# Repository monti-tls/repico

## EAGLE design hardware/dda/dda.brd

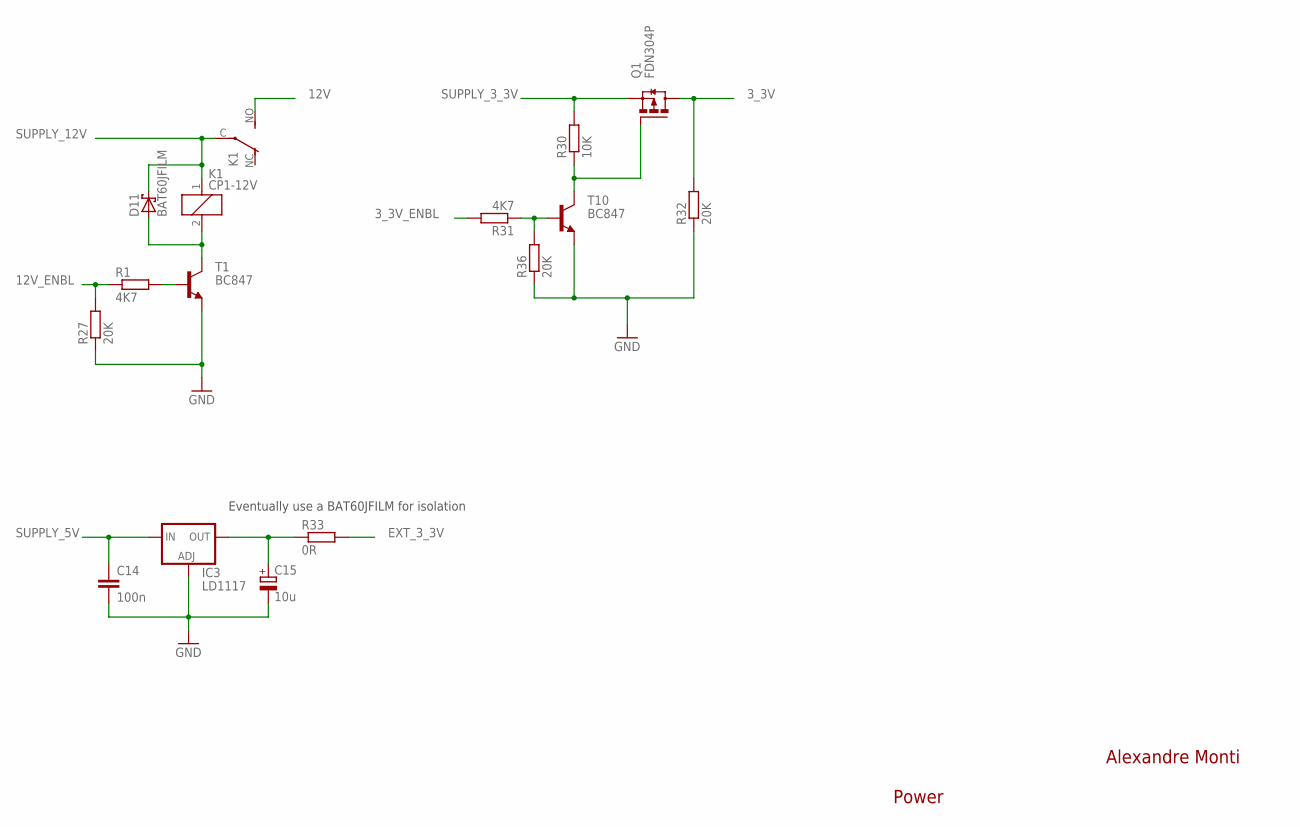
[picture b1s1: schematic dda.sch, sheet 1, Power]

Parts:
C14: 100n; C0805; PARTNO 2496944
C15: 10u; CT3216; PARTNO 1432339
D11: BAT60JFILM; SOD323_ST; PARTNO 1467544
IC3: LD1117; SOT223; PARTNO 1202826
K1: CP1-12V; CP1; PARTNO 2103582
Q1: FDN304P; SUPER-SOT3; PARTNO 9846298
R1, R31: 4K7; M0805; PARTNO 9333266
R27, R32, R36: 20K; M0805; PARTNO 9332774
R30: 10K; M0805; PARTNO 9332391
R33: 0R; R0805W; PARTNO 9333681
T1, T10: BC847; SOT23; PARTNO 2432696

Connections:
3_3V: Q1.3 (D), R32.2; also elsewhere on the board
3_3V_ENBL: R31.2; also elsewhere on the board
12V: K1.NO (S); also elsewhere on the board
12V_ENBL: R1.1, R27.2; also elsewhere on the board
EXT_3_3V: R33.2; also elsewhere on the board
GND: C14.2, C15.-, IC3.1 (ADJ), R27.1, R32.1, R36.1, T1.2 (E), T10.2 (E); also elsewhere on the board
unnamed: Q1.1 (G), R30.1, T10.3 (C)
unnamed: R31.1, R36.2, T10.1 (B)
unnamed: C15.+, IC3.4 (OUT), R33.1
unnamed: D11.A, K1.2, T1.3 (C)
unnamed: R1.2, T1.1 (B)
SUPPLY_3_3V: Q1.2 (S), R30.2; also elsewhere on the board
SUPPLY_5V: C14.1, IC3.3 (IN); also elsewhere on the board
SUPPLY_12V: D11.C, K1.1, K1.C; also elsewhere on the board

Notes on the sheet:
Alexandre Monti
Eventually use a BAT60JFILM for isolation
Power

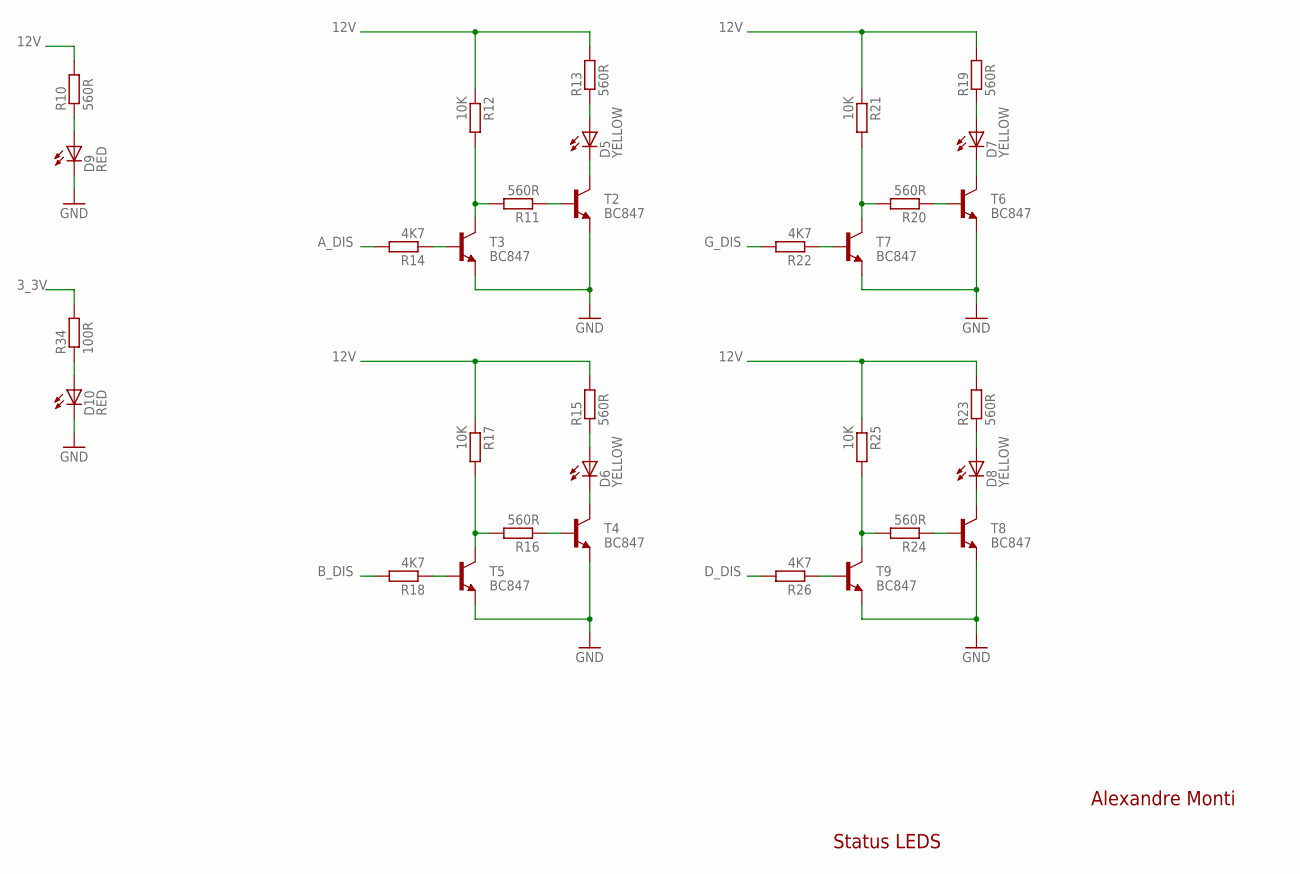
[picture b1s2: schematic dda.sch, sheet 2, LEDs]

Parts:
D5, D6, D7, D8: YELLOW; CHIP-LED0805; PARTNO 1581241
D9, D10: RED; CHIP-LED0805; PARTNO 1581239
R10, R11, R13, R15, R16, R19, R20, R23, R24: 560R; M0805; PARTNO 9334688
R12, R17, R21, R25: 10K; M0805; PARTNO 9332391
R14, R18, R22, R26: 4K7; M0805; PARTNO 9333266
R34: 100R; M0805; PARTNO 9237364
T2, T3, T4, T5, T6, T7, T8, T9: BC847; SOT23; PARTNO 2432696

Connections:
3_3V: R34.2; also elsewhere on the board
12V: R10.2, R12.1, R13.2, R15.2, R17.1, R19.2, R21.1, R23.2, R25.1; also elsewhere on the board
A_DIS: R14.2; also elsewhere on the board
B_DIS: R18.2; also elsewhere on the board
D_DIS: R26.2; also elsewhere on the board
GND: D9.C, D10.C, T2.2 (E), T3.2 (E), T4.2 (E), T5.2 (E), T6.2 (E), T7.2 (E), T8.2 (E), T9.2 (E); also elsewhere on the board
G_DIS: R22.2; also elsewhere on the board
unnamed: D10.A, R34.1
unnamed: D5.C, T2.3 (C)
unnamed: D5.A, R13.1
unnamed: R11.1, T2.1 (B)
unnamed: R11.2, R12.2, T3.3 (C)
unnamed: D6.C, T4.3 (C)
unnamed: R14.1, T3.1 (B)
unnamed: D6.A, R15.1
unnamed: R16.1, T4.1 (B)
unnamed: R16.2, R17.2, T5.3 (C)
unnamed: R18.1, T5.1 (B)
unnamed: D7.C, T6.3 (C)
unnamed: D7.A, R19.1
unnamed: R20.1, T6.1 (B)
unnamed: R20.2, R21.2, T7.3 (C)
unnamed: R22.1, T7.1 (B)
unnamed: D8.C, T8.3 (C)
unnamed: D8.A, R23.1
unnamed: R24.1, T8.1 (B)
unnamed: R24.2, R25.2, T9.3 (C)
unnamed: R26.1, T9.1 (B)
unnamed: D9.A, R10.1

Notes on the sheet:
Alexandre Monti
Status LEDS

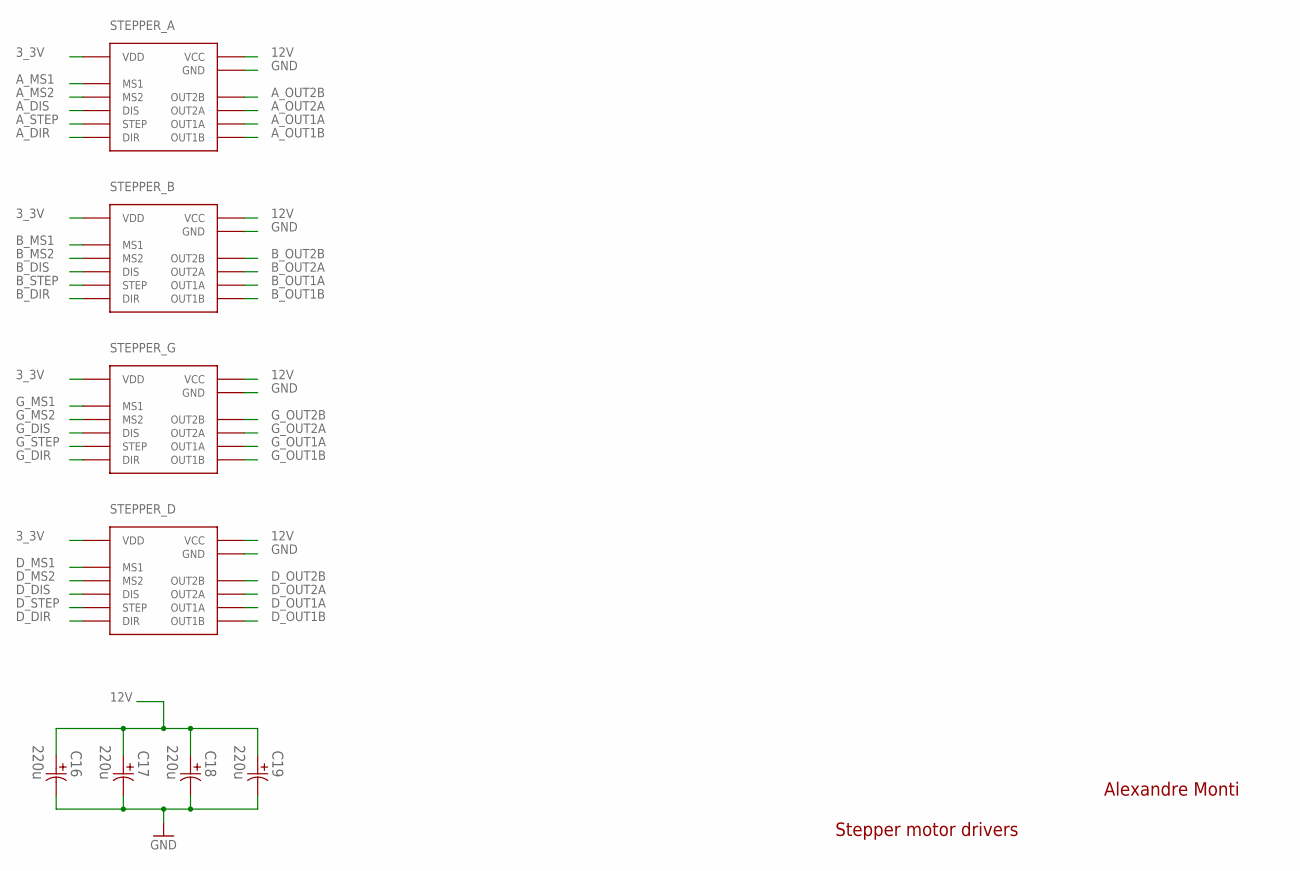
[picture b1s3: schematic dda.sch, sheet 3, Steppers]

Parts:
C16, C17, C18, C19: 220u; CAPAE660X800N; PARTNO 1868409
STEPPER_A: REPICO_STEPPER; PARTNO 1593462
STEPPER_B: REPICO_STEPPER; PARTNO 1593462
STEPPER_D: REPICO_STEPPER; PARTNO 1593462
STEPPER_G: REPICO_STEPPER; PARTNO 1593462

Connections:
3_3V: STEPPER_A.VDD, STEPPER_B.VDD, STEPPER_D.VDD, STEPPER_G.VDD; also elsewhere on the board
12V: C16.1, C17.1, C18.1, C19.1, STEPPER_A.VCC, STEPPER_B.VCC, STEPPER_D.VCC, STEPPER_G.VCC; also elsewhere on the board
A_DIR: STEPPER_A.DIR; also elsewhere on the board
A_DIS: STEPPER_A.DIS; also elsewhere on the board
A_MS1: STEPPER_A.MS1; also elsewhere on the board
A_MS2: STEPPER_A.MS2; also elsewhere on the board
A_OUT1A: STEPPER_A.OUT1A; also elsewhere on the board
A_OUT1B: STEPPER_A.OUT1B; also elsewhere on the board
A_OUT2A: STEPPER_A.OUT2A; also elsewhere on the board
A_OUT2B: STEPPER_A.OUT2B; also elsewhere on the board
A_STEP: STEPPER_A.STEP; also elsewhere on the board
B_DIR: STEPPER_B.DIR; also elsewhere on the board
B_DIS: STEPPER_B.DIS; also elsewhere on the board
B_MS1: STEPPER_B.MS1; also elsewhere on the board
B_MS2: STEPPER_B.MS2; also elsewhere on the board
B_OUT1A: STEPPER_B.OUT1A; also elsewhere on the board
B_OUT1B: STEPPER_B.OUT1B; also elsewhere on the board
B_OUT2A: STEPPER_B.OUT2A; also elsewhere on the board
B_OUT2B: STEPPER_B.OUT2B; also elsewhere on the board
B_STEP: STEPPER_B.STEP; also elsewhere on the board
D_DIR: STEPPER_D.DIR; also elsewhere on the board
D_DIS: STEPPER_D.DIS; also elsewhere on the board
D_MS1: STEPPER_D.MS1; also elsewhere on the board
D_MS2: STEPPER_D.MS2; also elsewhere on the board
D_OUT1A: STEPPER_D.OUT1A; also elsewhere on the board
D_OUT1B: STEPPER_D.OUT1B; also elsewhere on the board
D_OUT2A: STEPPER_D.OUT2A; also elsewhere on the board
D_OUT2B: STEPPER_D.OUT2B; also elsewhere on the board
D_STEP: STEPPER_D.STEP; also elsewhere on the board
GND: C16.2, C17.2, C18.2, C19.2, STEPPER_A.GND, STEPPER_B.GND, STEPPER_D.GND, STEPPER_G.GND; also elsewhere on the board
G_DIR: STEPPER_G.DIR; also elsewhere on the board
G_DIS: STEPPER_G.DIS; also elsewhere on the board
G_MS1: STEPPER_G.MS1; also elsewhere on the board
G_MS2: STEPPER_G.MS2; also elsewhere on the board
G_OUT1A: STEPPER_G.OUT1A; also elsewhere on the board
G_OUT1B: STEPPER_G.OUT1B; also elsewhere on the board
G_OUT2A: STEPPER_G.OUT2A; also elsewhere on the board
G_OUT2B: STEPPER_G.OUT2B; also elsewhere on the board
G_STEP: STEPPER_G.STEP; also elsewhere on the board

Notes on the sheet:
Stepper motor drivers
Alexandre Monti

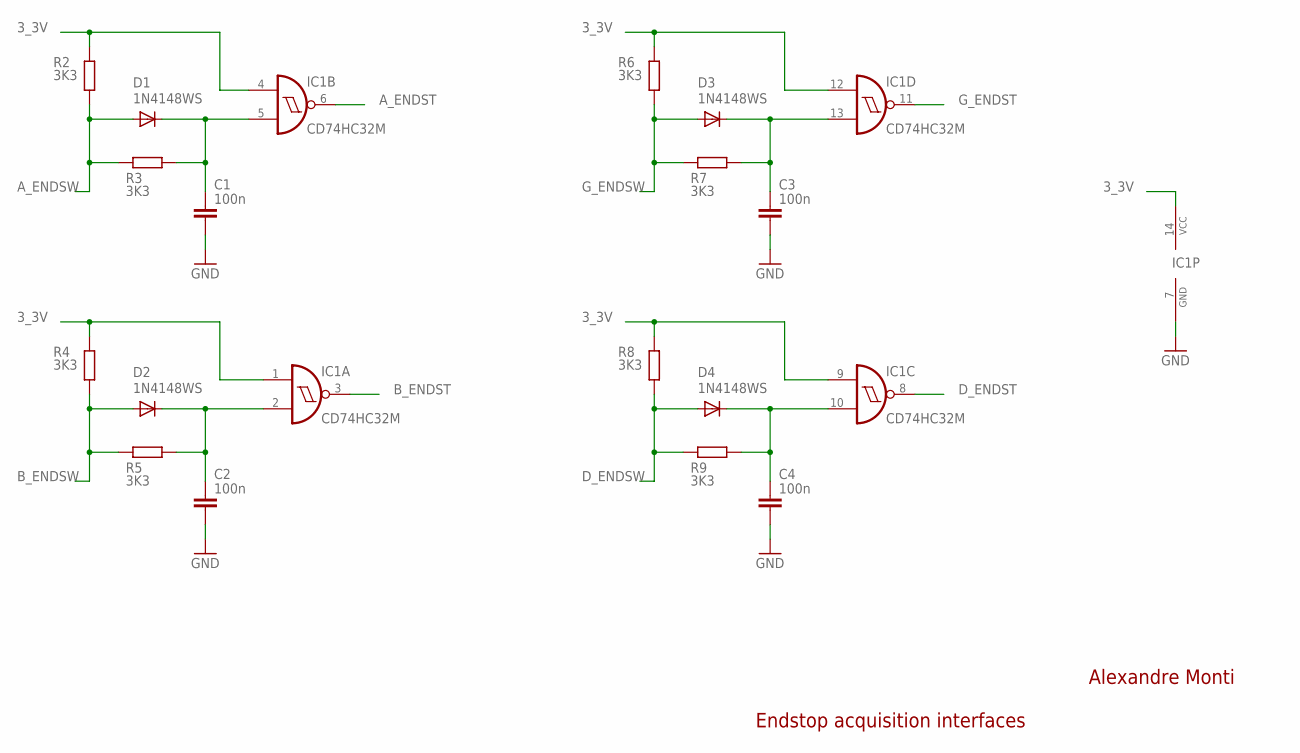
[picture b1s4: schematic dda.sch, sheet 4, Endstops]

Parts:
C1, C2, C3, C4: 100n; C0805; PARTNO 2496944
D1, D2, D3, D4: 1N4148WS; SOD123; PARTNO 1466524
IC1: CD74HC32M; SO14; PARTNO 1103158
R2, R3, R4, R5, R6, R7, R8, R9: 3K3; M0805; PARTNO 9333045

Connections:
3_3V: IC1.1 (I0), IC1.4 (I0), IC1.9 (I0), IC1.12 (I0), IC1.14 (VCC), R2.2, R4.2, R6.2, R8.2; also elsewhere on the board
A_ENDST: IC1.6 (O); also elsewhere on the board
A_ENDSW: D1.A, R2.1, R3.1; also elsewhere on the board
B_ENDST: IC1.3 (O); also elsewhere on the board
B_ENDSW: D2.A, R4.1, R5.1; also elsewhere on the board
D_ENDST: IC1.8 (O); also elsewhere on the board
D_ENDSW: D4.A, R8.1, R9.1; also elsewhere on the board
GND: C1.2, C2.2, C3.2, C4.2, IC1.7 (GND); also elsewhere on the board
G_ENDST: IC1.11 (O); also elsewhere on the board
G_ENDSW: D3.A, R6.1, R7.1; also elsewhere on the board
unnamed: C1.1, D1.C, IC1.5 (I1), R3.2
unnamed: C2.1, D2.C, IC1.2 (I1), R5.2
unnamed: C3.1, D3.C, IC1.13 (I1), R7.2
unnamed: C4.1, D4.C, IC1.10 (I1), R9.2

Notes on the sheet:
Alexandre Monti
Endstop acquisition interfaces

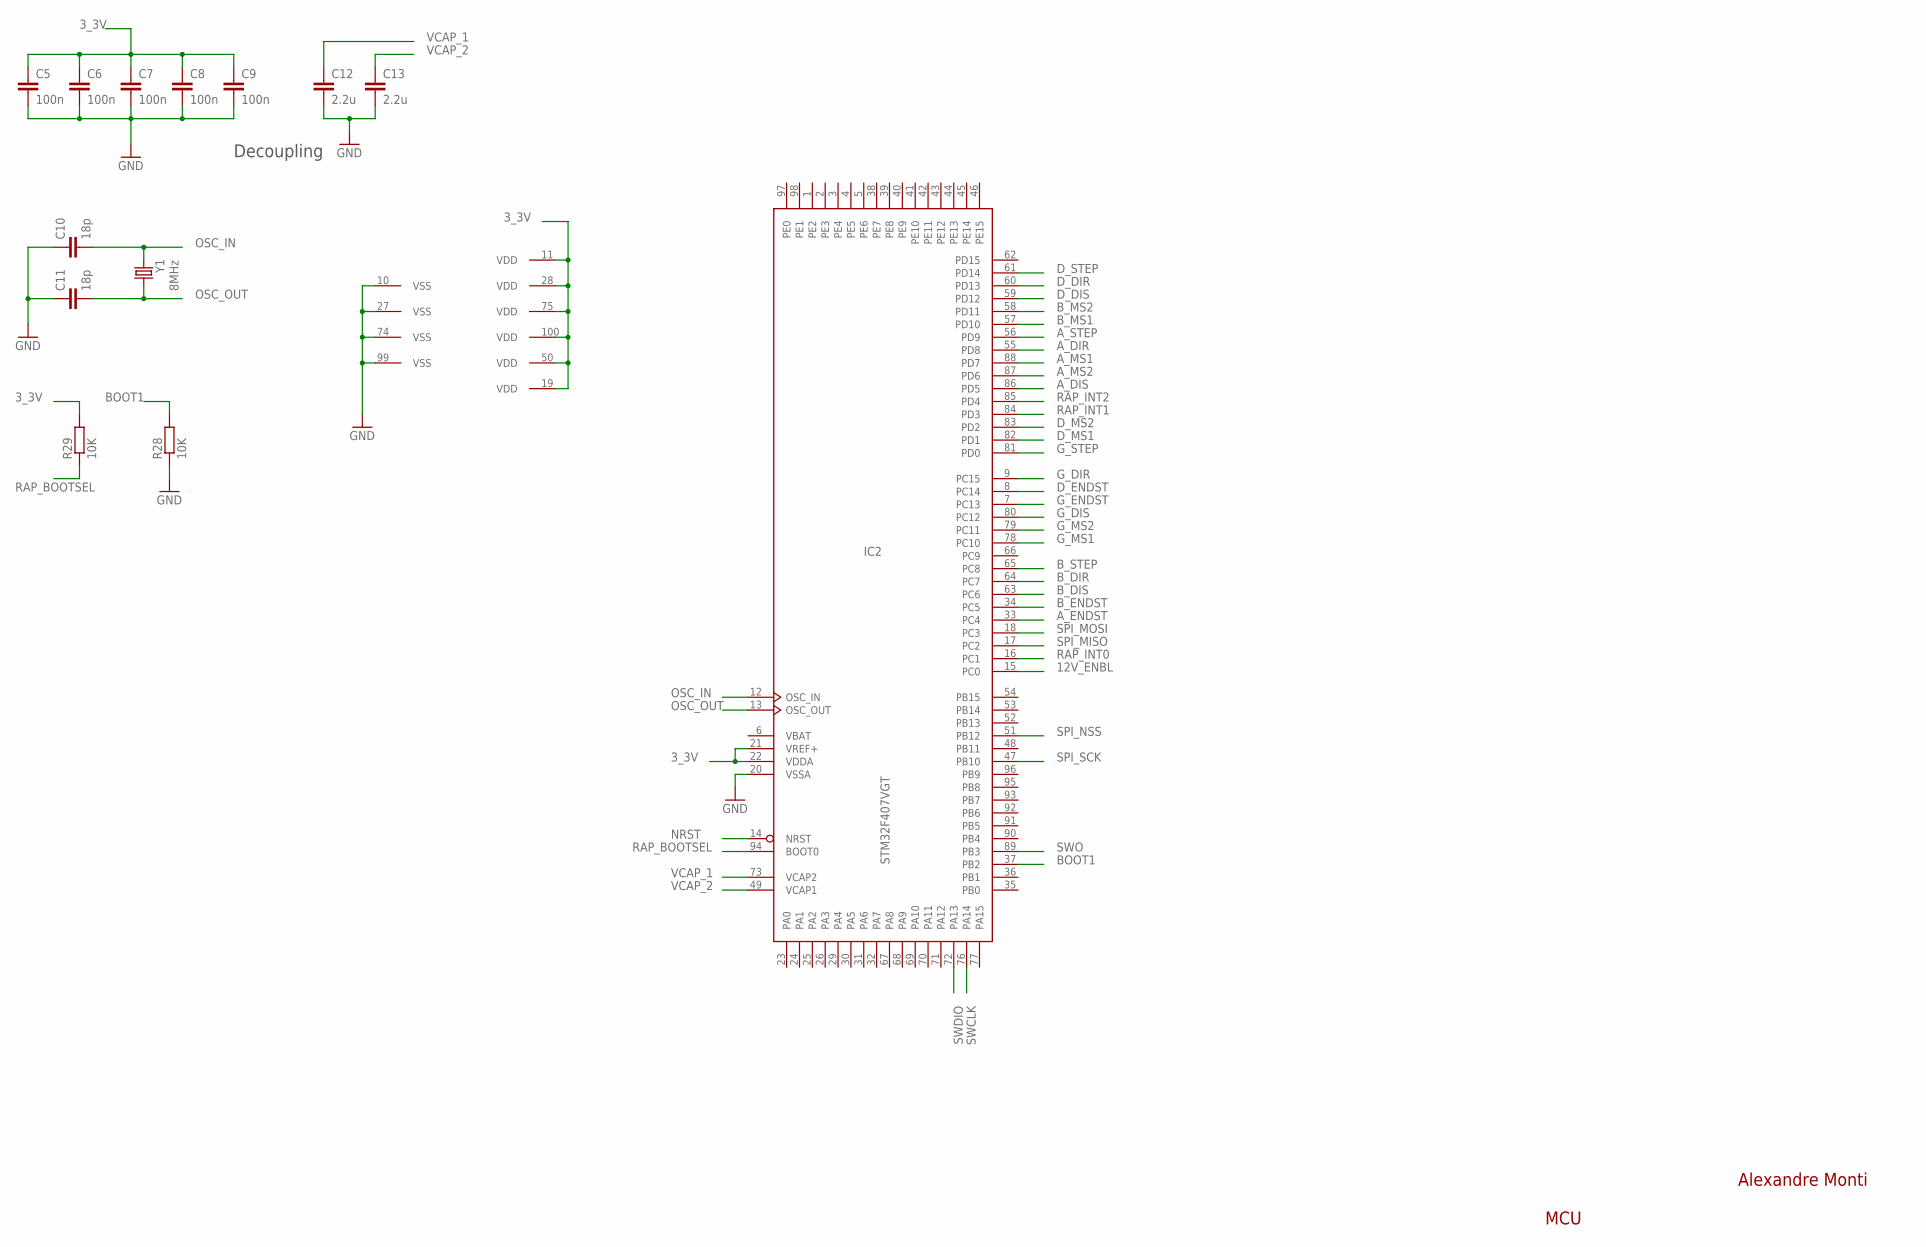
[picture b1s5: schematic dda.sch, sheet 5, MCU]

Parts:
C5, C6, C7, C8, C9: 100n; C0805; PARTNO 2496944
C10, C11: 18p; C0805; PARTNO 1414673
C12, C13: 2.2u; C1206; PARTNO 1759477
IC2: STM32F407VGT; LQFP100; PARTNO 2064368
R28, R29: 10K; M0805; PARTNO 9332391
Y1: 8MHz; CRYSTAL-SMD-5X3.2; PARTNO 2101329

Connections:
3_3V: C5.1, C6.1, C7.1, C8.1, C9.1, IC2.11 (VDD), IC2.19 (VDD), IC2.21 (VREF+), IC2.22 (VDDA), IC2.28 (VDD), IC2.50 (VDD), IC2.75 (VDD), IC2.100 (VDD), R29.2; also elsewhere on the board
12V_ENBL: IC2.15 (PC0); also elsewhere on the board
A_DIR: IC2.55 (PD8); also elsewhere on the board
A_DIS: IC2.86 (PD5); also elsewhere on the board
A_ENDST: IC2.33 (PC4); also elsewhere on the board
A_MS1: IC2.88 (PD7); also elsewhere on the board
A_MS2: IC2.87 (PD6); also elsewhere on the board
A_STEP: IC2.56 (PD9); also elsewhere on the board
BOOT1: IC2.37 (PB2), R28.2
B_DIR: IC2.64 (PC7); also elsewhere on the board
B_DIS: IC2.63 (PC6); also elsewhere on the board
B_ENDST: IC2.34 (PC5); also elsewhere on the board
B_MS1: IC2.57 (PD10); also elsewhere on the board
B_MS2: IC2.58 (PD11); also elsewhere on the board
B_STEP: IC2.65 (PC8); also elsewhere on the board
D_DIR: IC2.60 (PD13); also elsewhere on the board
D_DIS: IC2.59 (PD12); also elsewhere on the board
D_ENDST: IC2.8 (PC14); also elsewhere on the board
D_MS1: IC2.82 (PD1); also elsewhere on the board
D_MS2: IC2.83 (PD2); also elsewhere on the board
D_STEP: IC2.61 (PD14); also elsewhere on the board
GND: C5.2, C6.2, C7.2, C8.2, C9.2, C10.1, C11.1, C12.2, C13.2, IC2.10 (VSS), IC2.20 (VSSA), IC2.27 (VSS), IC2.74 (VSS), IC2.99 (VSS), R28.1; also elsewhere on the board
G_DIR: IC2.9 (PC15); also elsewhere on the board
G_DIS: IC2.80 (PC12); also elsewhere on the board
G_ENDST: IC2.7 (PC13); also elsewhere on the board
G_MS1: IC2.78 (PC10); also elsewhere on the board
G_MS2: IC2.79 (PC11); also elsewhere on the board
G_STEP: IC2.81 (PD0); also elsewhere on the board
NRST: IC2.14 (NRST); also elsewhere on the board
OSC_IN: C10.2, IC2.12 (OSC_IN), Y1.P$2 (2)
OSC_OUT: C11.2, IC2.13 (OSC_OUT), Y1.P$1 (1)
RAP_BOOTSEL: IC2.94 (BOOT0), R29.1; also elsewhere on the board
RAP_INT0: IC2.16 (PC1); also elsewhere on the board
RAP_INT1: IC2.84 (PD3); also elsewhere on the board
RAP_INT2: IC2.85 (PD4); also elsewhere on the board
SPI_MISO: IC2.17 (PC2); also elsewhere on the board
SPI_MOSI: IC2.18 (PC3); also elsewhere on the board
SPI_NSS: IC2.51 (PB12); also elsewhere on the board
SPI_SCK: IC2.47 (PB10); also elsewhere on the board
SWCLK: IC2.76 (PA14); also elsewhere on the board
SWDIO: IC2.72 (PA13); also elsewhere on the board
SWO: IC2.89 (PB3); also elsewhere on the board
VBAT: IC2.6 (VBAT)
VCAP_1: C12.1, IC2.73 (VCAP2)
VCAP_2: C13.1, IC2.49 (VCAP1)

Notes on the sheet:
Decoupling
Alexandre Monti
MCU

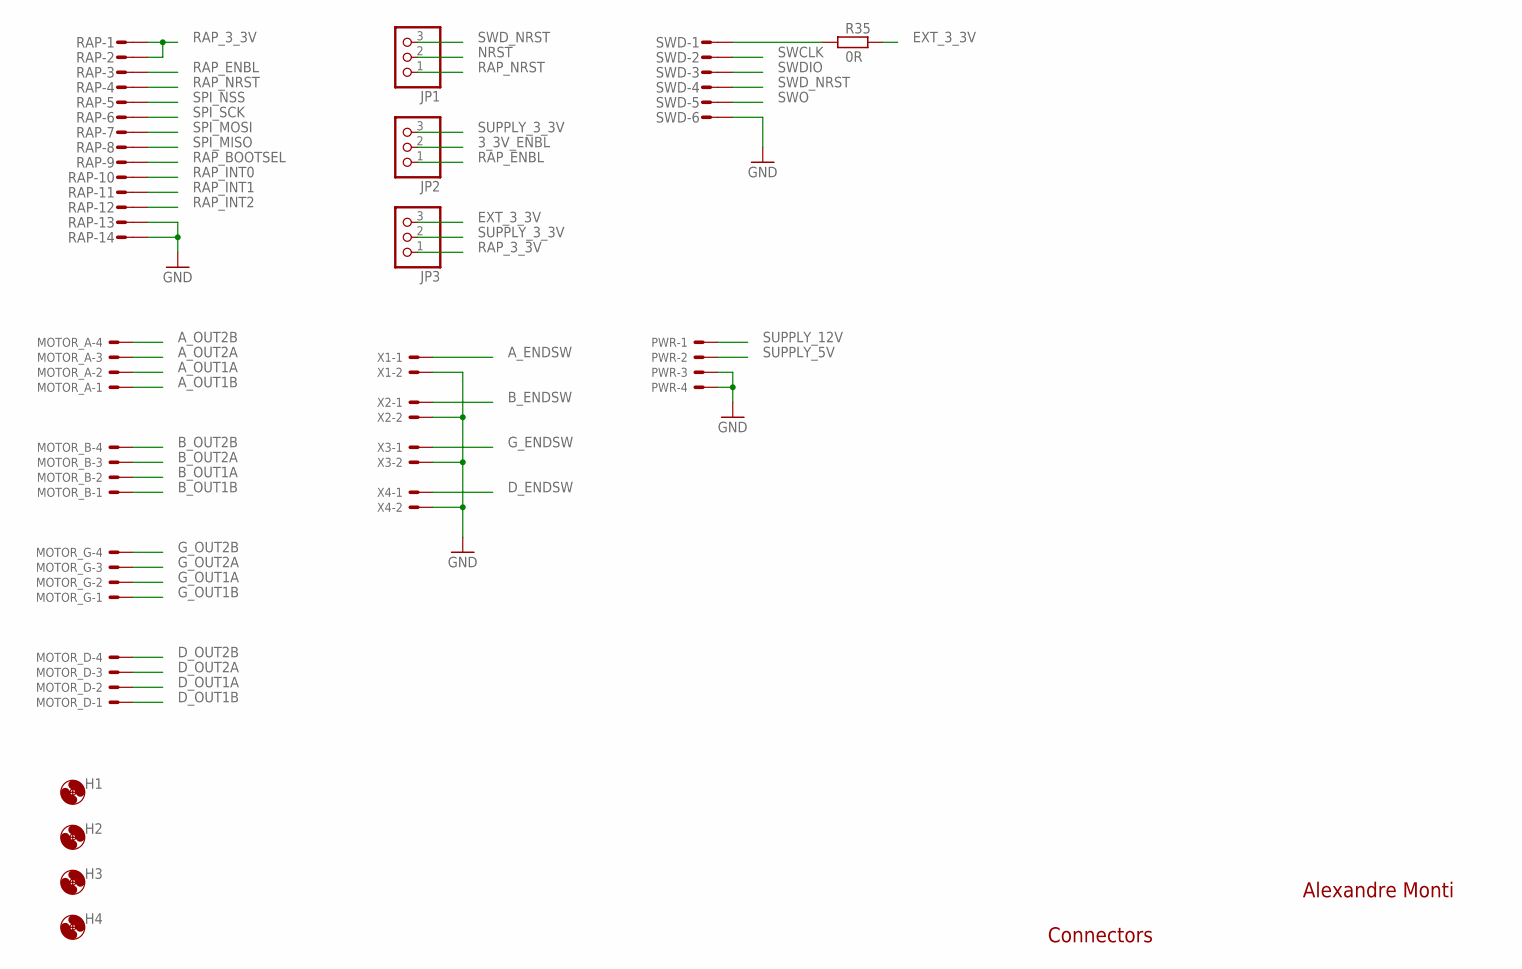
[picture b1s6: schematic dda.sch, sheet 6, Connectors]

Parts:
H1, H2, H3, H4: MOUNT-HOLE3.2; 3,2
JP1, JP2, JP3: PINHD-1X03_2.00; 1X03M; PARTNO 2289777
MOTOR_A: 22-23-2041; PARTNO 588593
MOTOR_B: 22-23-2041; PARTNO 588593
MOTOR_D: 22-23-2041; PARTNO 588593
MOTOR_G: 22-23-2041; PARTNO 588593
PWR: 22-23-2041; PARTNO 588593
R35: 0R; R0805W; PARTNO 9333681
RAP: MICROMATCH-14; MATE_PARTNO 149135
SWD: MICROMATCH-6; MATE_PARTNO 149068
X1, X2, X3, X4: 22-23-2021; PARTNO 588570

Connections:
3_3V_ENBL: JP2.2; also elsewhere on the board
A_ENDSW: X1.1; also elsewhere on the board
A_OUT1A: MOTOR_A.2; also elsewhere on the board
A_OUT1B: MOTOR_A.1; also elsewhere on the board
A_OUT2A: MOTOR_A.3; also elsewhere on the board
A_OUT2B: MOTOR_A.4; also elsewhere on the board
B_ENDSW: X2.1; also elsewhere on the board
B_OUT1A: MOTOR_B.2; also elsewhere on the board
B_OUT1B: MOTOR_B.1; also elsewhere on the board
B_OUT2A: MOTOR_B.3; also elsewhere on the board
B_OUT2B: MOTOR_B.4; also elsewhere on the board
D_ENDSW: X4.1; also elsewhere on the board
D_OUT1A: MOTOR_D.2; also elsewhere on the board
D_OUT1B: MOTOR_D.1; also elsewhere on the board
D_OUT2A: MOTOR_D.3; also elsewhere on the board
D_OUT2B: MOTOR_D.4; also elsewhere on the board
EXT_3_3V: JP3.3, R35.2; also elsewhere on the board
GND: PWR.3, PWR.4, RAP.13, RAP.14, SWD.6, X1.2, X2.2, X3.2, X4.2; also elsewhere on the board
G_ENDSW: X3.1; also elsewhere on the board
G_OUT1A: MOTOR_G.2; also elsewhere on the board
G_OUT1B: MOTOR_G.1; also elsewhere on the board
G_OUT2A: MOTOR_G.3; also elsewhere on the board
G_OUT2B: MOTOR_G.4; also elsewhere on the board
unnamed: R35.1, SWD.1
NRST: JP1.2; also elsewhere on the board
RAP_3_3V: JP3.1, RAP.1, RAP.2
RAP_BOOTSEL: RAP.9; also elsewhere on the board
RAP_ENBL: JP2.1, RAP.3
RAP_INT0: RAP.10; also elsewhere on the board
RAP_INT1: RAP.11; also elsewhere on the board
RAP_INT2: RAP.12; also elsewhere on the board
RAP_NRST: JP1.1, RAP.4
SPI_MISO: RAP.8; also elsewhere on the board
SPI_MOSI: RAP.7; also elsewhere on the board
SPI_NSS: RAP.5; also elsewhere on the board
SPI_SCK: RAP.6; also elsewhere on the board
SUPPLY_3_3V: JP2.3, JP3.2; also elsewhere on the board
SUPPLY_5V: PWR.2; also elsewhere on the board
SUPPLY_12V: PWR.1; also elsewhere on the board
SWCLK: SWD.2; also elsewhere on the board
SWDIO: SWD.3; also elsewhere on the board
SWD_NRST: JP1.3, SWD.4
SWO: SWD.5; also elsewhere on the board

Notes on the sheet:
Alexandre Monti
Connectors

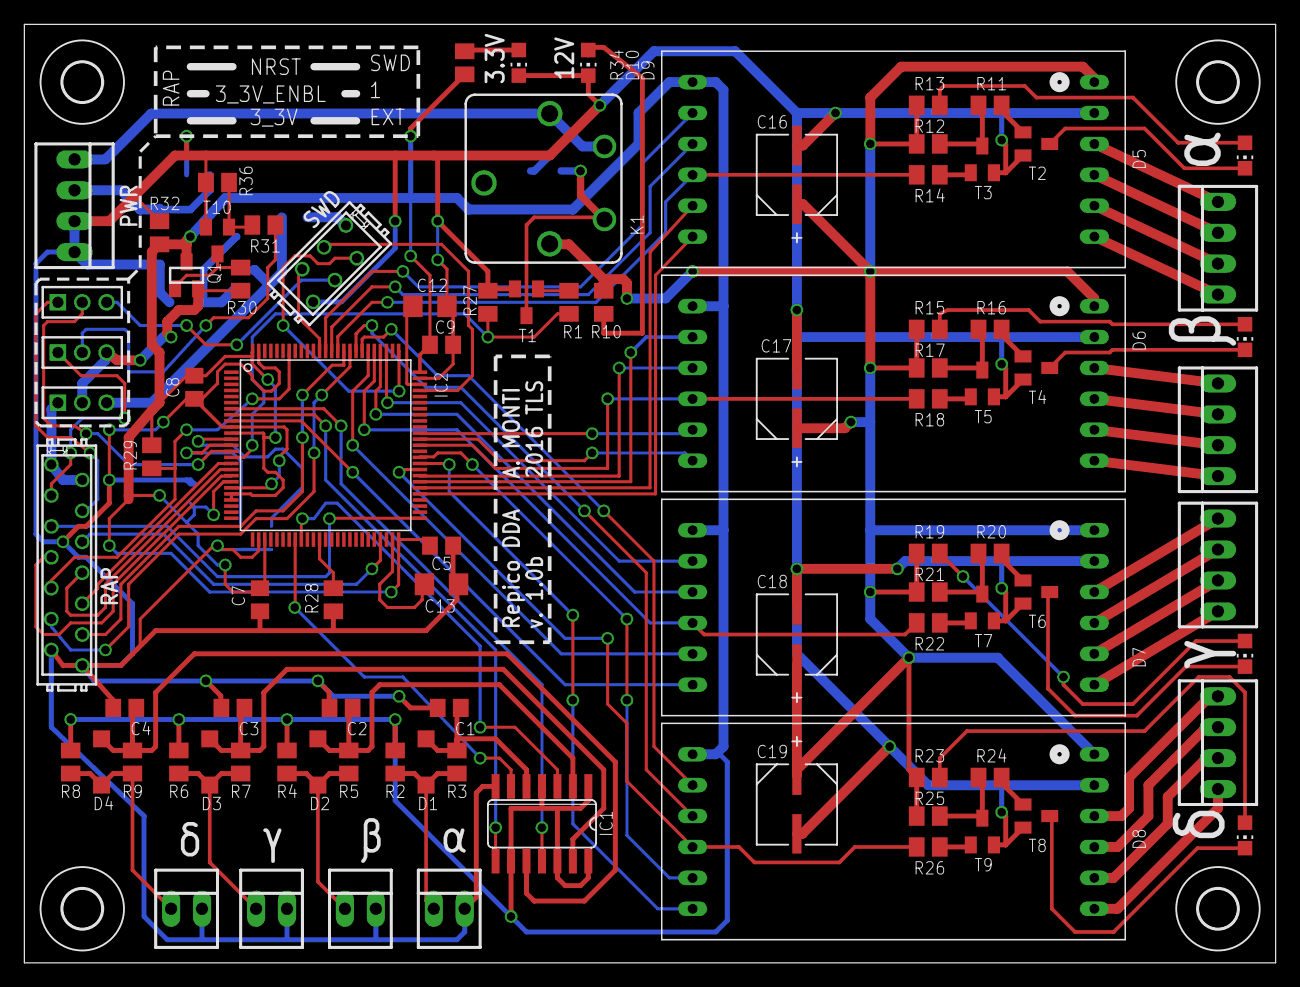
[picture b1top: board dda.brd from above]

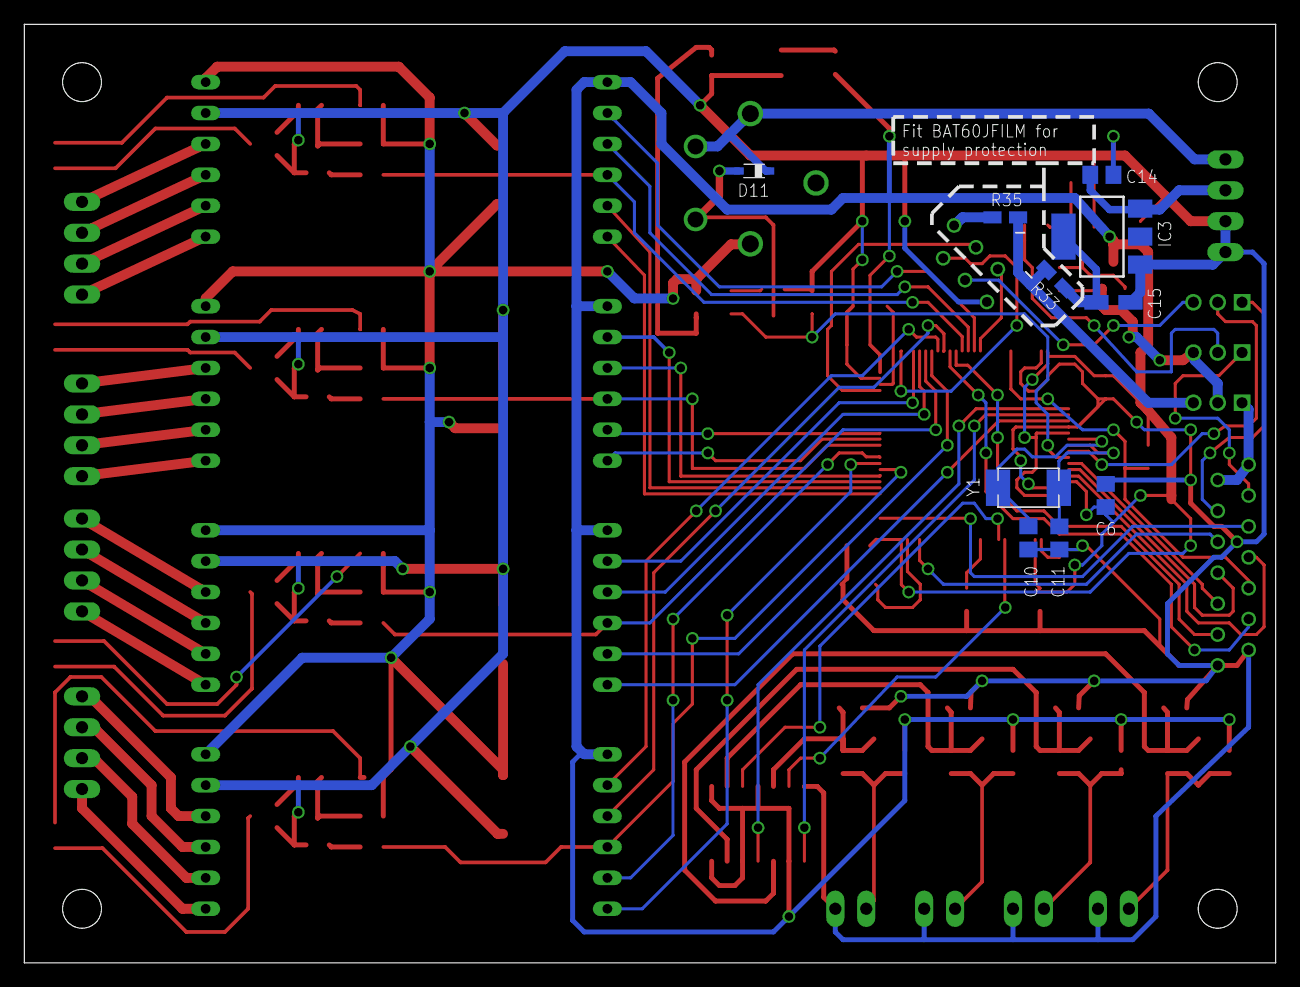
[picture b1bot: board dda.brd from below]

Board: 2 copper layers, 102.8 x 77.1 mm, 104 parts (10 on the bottom side), 106 nets.

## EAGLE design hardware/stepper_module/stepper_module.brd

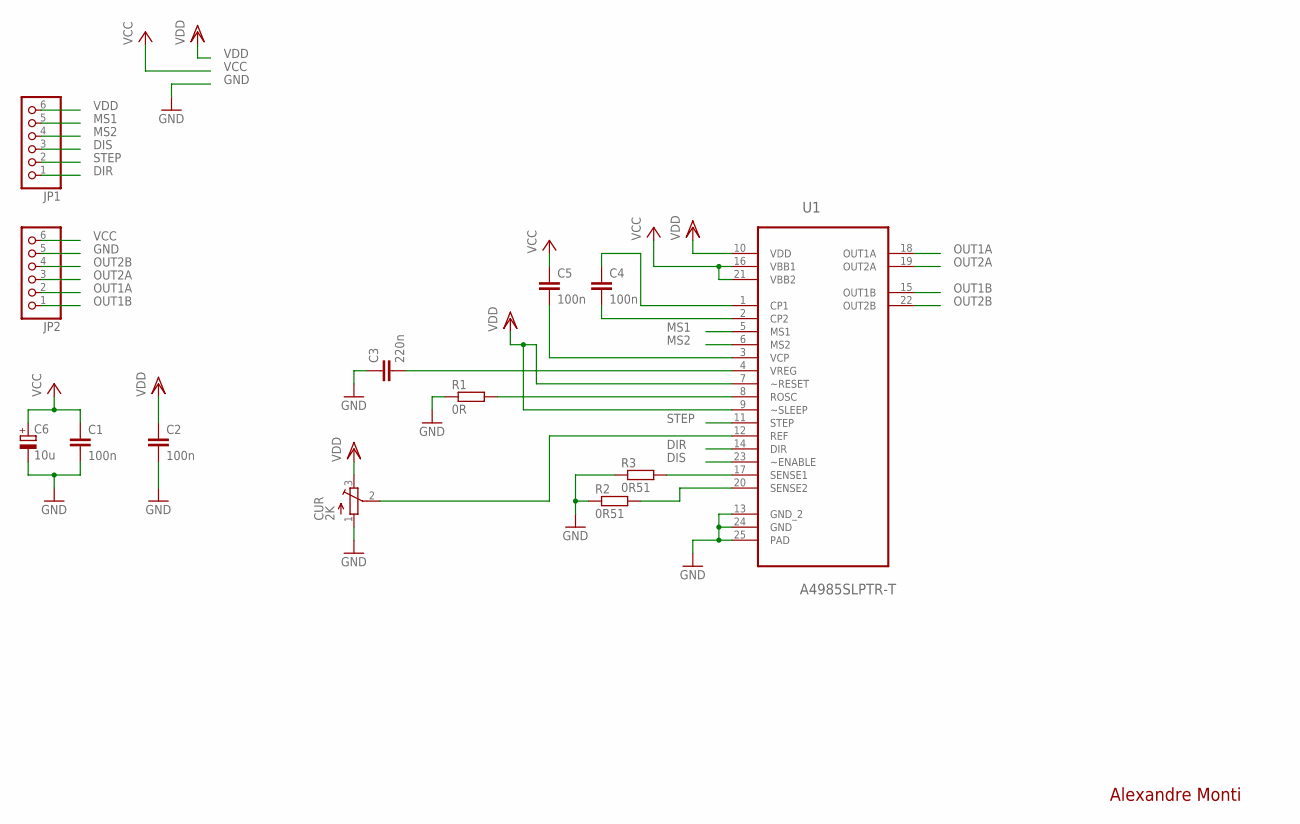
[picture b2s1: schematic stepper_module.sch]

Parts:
C1, C2, C4, C5: 100n; C0805
C3: 220n; C0805
C6: 10u; SMC_B
CUR: 2K; TC33X
JP1, JP2: PINHD-1X6; 1X06
R1: 0R; R0805
R2, R3: 0R51; R0805
U1: A4985SLPTR-T; SOP65P640X120-25N

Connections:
DIR: JP1.1, U1.14 (DIR)
DIS: JP1.3, U1.23 (~ENABLE)
GND: C1.2, C2.2, C3.1, C6.-, CUR.1 (A), JP2.5, R1.1, R2.1, R3.1, U1.13 (GND_2), U1.24 (GND), U1.25 (PAD)
MS1: JP1.5, U1.5 (MS1)
MS2: JP1.4, U1.6 (MS2)
unnamed: C4.2, U1.2 (CP2)
unnamed: C4.1, U1.1 (CP1)
unnamed: C5.2, U1.3 (VCP)
unnamed: C3.2, U1.4 (VREG)
unnamed: R3.2, U1.17 (SENSE1)
unnamed: R2.2, U1.20 (SENSE2)
unnamed: R1.2, U1.8 (ROSC)
unnamed: CUR.2 (S), U1.12 (REF)
OUT1A: JP2.2, U1.18 (OUT1A)
OUT1B: JP2.1, U1.15 (OUT1B)
OUT2A: JP2.3, U1.19 (OUT2A)
OUT2B: JP2.4, U1.22 (OUT2B)
STEP: JP1.2, U1.11 (STEP)
VCC: C1.1, C5.1, C6.+, JP2.6, U1.16 (VBB1), U1.21 (VBB2)
VDD: C2.1, CUR.3 (E), JP1.6, U1.7 (~RESET), U1.9 (~SLEEP), U1.10 (VDD)

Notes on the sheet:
Alexandre Monti

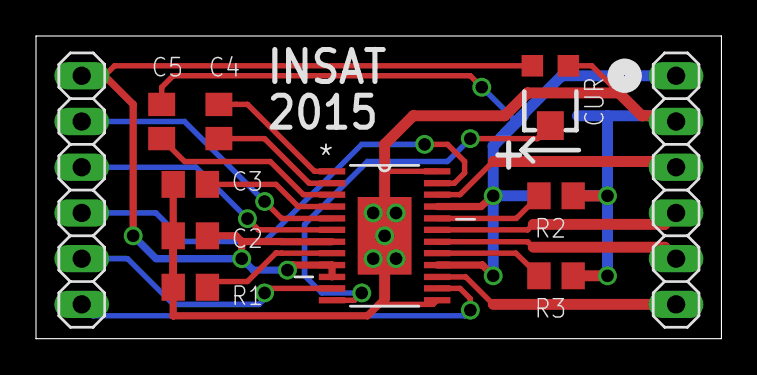
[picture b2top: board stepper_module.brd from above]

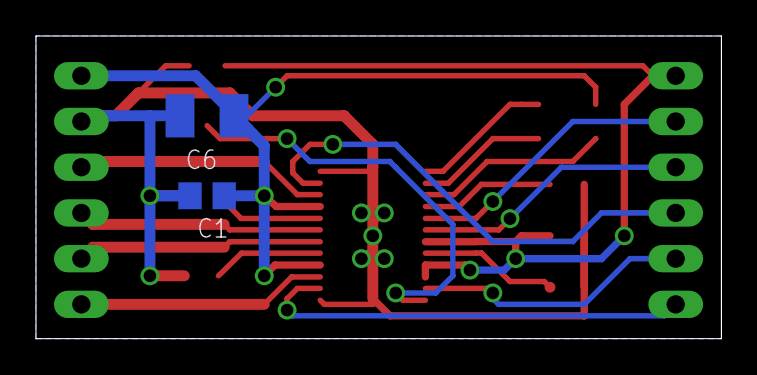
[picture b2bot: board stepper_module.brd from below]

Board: 2 copper layers, 38.1 x 16.8 mm, 13 parts (2 on the bottom side), 20 nets.

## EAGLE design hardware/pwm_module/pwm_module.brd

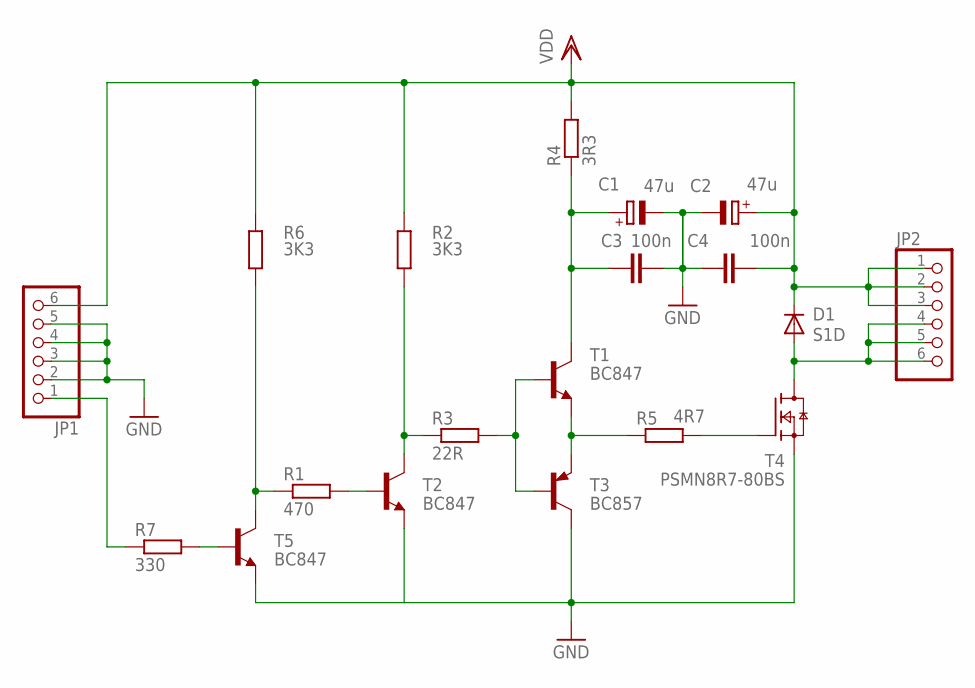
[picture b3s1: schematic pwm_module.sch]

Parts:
C1, C2: 47u; PANASONIC_F; FARNELL 9696032
C3, C4: 100n; C1206K; FARNELL 1759366
D1: S1D; DO-214AC; FARNELL 2454091
JP1, JP2: PINHD-1X6; 1X06
R1: 470; M0805
R2, R6: 3K3; M0805
R3: 22R; M0805
R4: 3R3; M0805
R5: 4R7; M0805
R7: 330; M0805
T1, T2, T5: BC847; SOT23; FARNELL 2432696
T3: BC857; SOT23-BEC; FARNELL 8734771
T4: PSMN8R7-80BS; SOT404; FARNELL 2112547

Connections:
GND: C1.-, C2.-, C3.2, C4.2, JP1.2, JP1.3, JP1.4, JP1.5, T2.2 (E), T3.C, T4.3 (S), T5.2 (E)
unnamed: R5.1, T1.2 (E), T3.E
unnamed: R5.2, T4.1 (G)
unnamed: R3.2, T1.1 (B), T3.B
unnamed: R2.1, R3.1, T2.3 (C)
unnamed: R1.2, T2.1 (B)
unnamed: JP1.1, R7.1
unnamed: D1.A, JP2.4, JP2.5, JP2.6, T4.MB (D)
unnamed: C1.+, C3.1, R4.1, T1.3 (C)
unnamed: R1.1, R6.1, T5.3 (C)
unnamed: R7.2, T5.1 (B)
V+: C2.+, C4.1, D1.C, JP1.6, JP2.1, JP2.2, JP2.3, R2.2, R4.2, R6.2

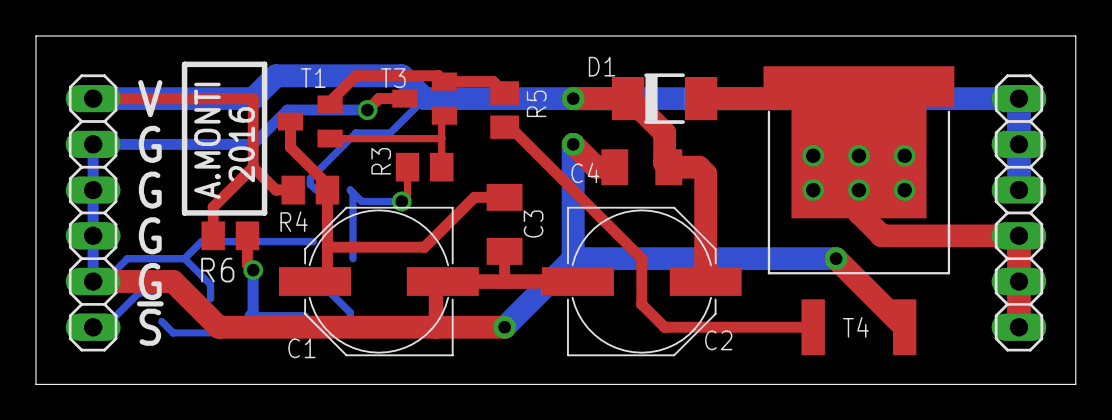
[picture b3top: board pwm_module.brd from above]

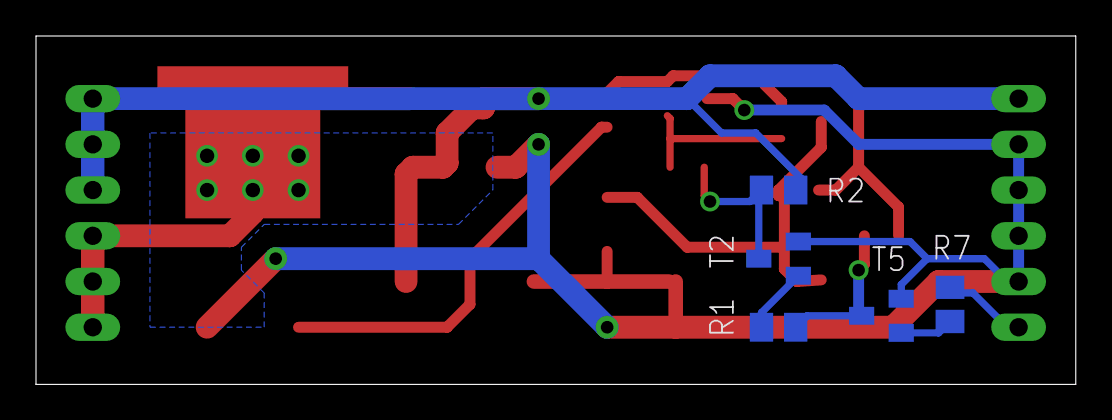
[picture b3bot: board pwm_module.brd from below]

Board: 2 copper layers, 57.8 x 19.4 mm, 19 parts (5 on the bottom side), 12 nets.

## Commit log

2015-11-12 Minor testing changes in bbb/rap
2015-11-12 Exploring DTBs and GPIOs
2015-11-12 Added SysFS support basis to bbb/modules/rap using kobject
2015-11-12 Minor changes to rapdev driver
2015-11-12 Added BBB side RAP over SPI basics
    - added a dvice tree overlay for SPI0 (to be renamed later)
    - added a RAP device driver module (empty for the moment, but correctly bound)
2015-11-12 Fixed SPI0 DTS file errors
2015-11-12 Added Kbuild file for kernel modules, added common/defs/ definitions for RAP
2015-11-12 Added RAP0 gpios to DTB
2015-11-12 RAP/SPI R/W works :)
2015-11-12 Fiddled with RAP SPI to have a full duplex communication (w/ 16 bit words)
2015-11-12 Added RAP kernel module shell
2015-11-13 Finally, SPI seems to work
2015-11-13 Added Netlink interface to rapdev kernel device driver with example userspace usage
2016-12-09 Added infrastructure + libecu and eifm project shells
2016-12-11 Finaly a correct example for SPI2 on the EIFM cortex
2016-12-12 Changed SPI word size to 16, works with RAP BBB module
2016-12-13 Added hardware / simulation parts :
    - existing stepper driver board (simplified)
    - new PWM module (untested), with LTSpice model
    - part of the DDA schematic / board with design LTSpice models
2016-12-15 Finally, SPI seems to work (ECU side)
2016-12-18 Added ecu/librap for RAP/SPI port, plus some refactoring
2016-12-18 Fixed include in libecu
2016-12-25 DDA board routed v1.0b
2016-12-25 Removed fucking +x bits from windowze
